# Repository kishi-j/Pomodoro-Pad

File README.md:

# Pomodoro Pad
Pomodoro Pad is a 3 key macropad with a rotary encoder and an OLED Display, using KMK firmware. It will act as a pomodoro timer with a start, pause/resume, and reset button, with the rotary encoder to set the timer length. (The firmware will be updated to work after the parts arrive.)

## CAD Model:

## PCB:

## Schematic:

## BOM:
- 3x Cherry MX Switches
- 3x DSA Keycaps
- 1x 0.91" 128x32 OLED Display
- 1x EC11 Rotary Encoder
- 1x XIAO RP2040
- 1x Case

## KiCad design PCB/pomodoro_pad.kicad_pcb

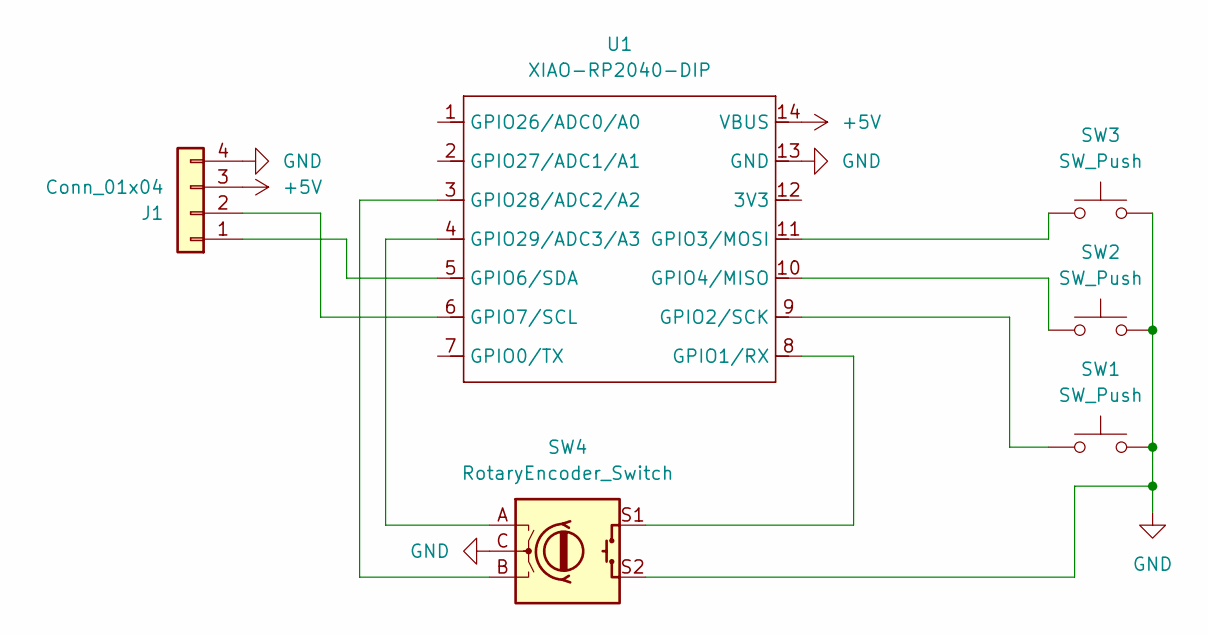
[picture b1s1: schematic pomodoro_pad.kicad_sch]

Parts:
J1: Conn_01x04; SSD1306-0.91-OLED-4pin-128x32
SW1, SW2, SW3: SW_Push; SW_Cherry_MX_1.00u_PCB
SW4: RotaryEncoder_Switch; RotaryEncoder_Alps_EC11E-Switch_Vertical_H20mm
U1: XIAO-RP2040-DIP

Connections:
+5V: J1.3, U1.14 (VBUS)
GND: J1.4, SW1.2, SW2.2, SW3.2, SW4.C, SW4.S2, U1.13 (GND)
unnamed: J1.1, U1.5 (GPIO6/SDA)
unnamed: J1.2, U1.6 (GPIO7/SCL)
unnamed: SW4.S1, U1.8 (GPIO1/RX)
unnamed: SW1.1, U1.9 (GPIO2/SCK)
unnamed: SW3.1, U1.11 (GPIO3/MOSI)
unnamed: SW2.1, U1.10 (GPIO4/MISO)
unnamed: SW4.B, U1.3 (GPIO28/ADC2/A2)
unnamed: SW4.A, U1.4 (GPIO29/ADC3/A3)

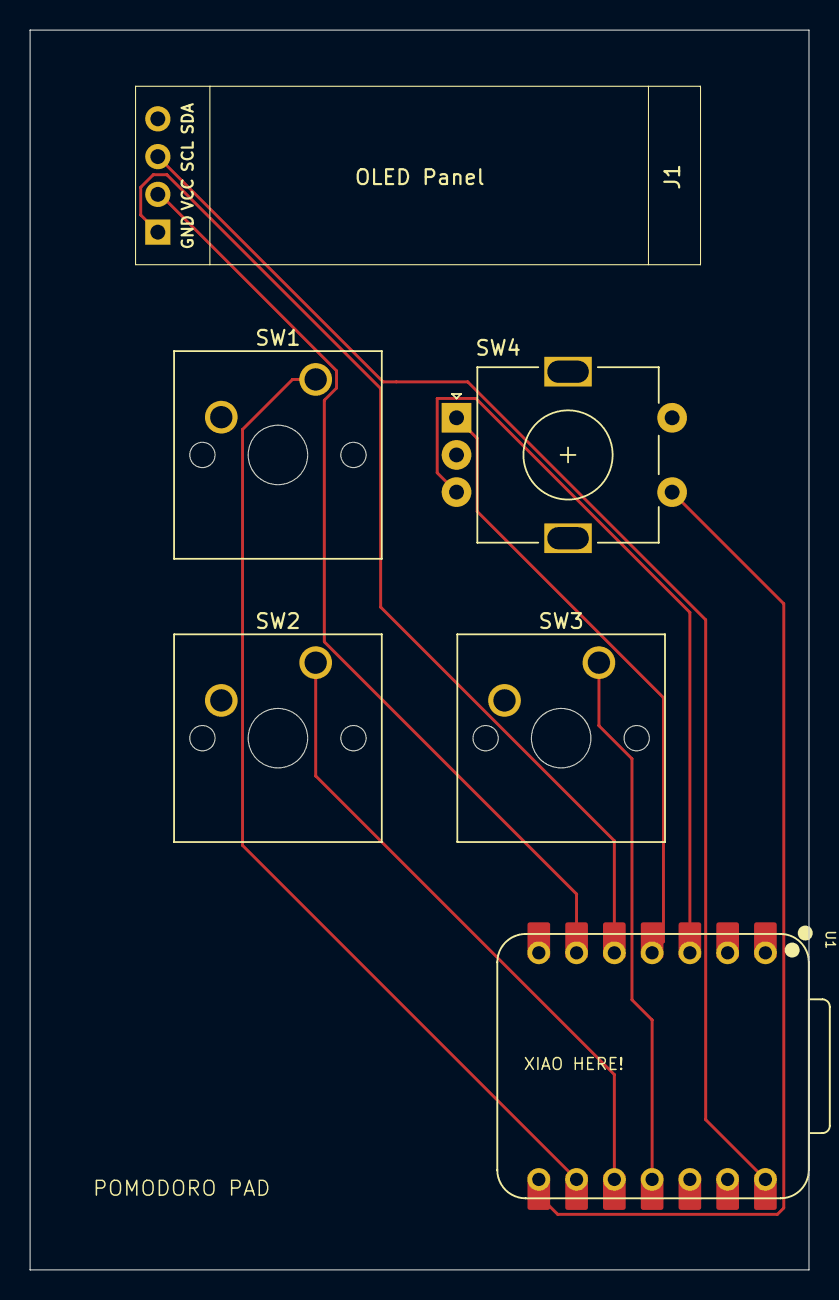
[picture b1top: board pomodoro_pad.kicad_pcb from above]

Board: 2 copper layers, 52.4 x 83.4 mm, 6 parts (0 on the bottom side), 10 nets.

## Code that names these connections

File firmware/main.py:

import board
import displayio
import busio
import adafruit_displayio_ssd1306
from kmk.kmk_keyboard import KMKKeyboard
from kmk.scanners.keypad import KeysScanner
from kmk.modules.encoder import EncoderHandler

displayio.release_displays()

i2c = busio.I2C(scl=board.D7, sda=board.D6)  # GPIO7 = SCL, GPIO6 = SDA
display_bus = displayio.I2CDisplay(i2c, device_address=0x3C)  # 0x3C is default SSD1306 I2C addr
display = adafruit_displayio_ssd1306.SSD1306(display_bus, width=128, height=64)

keyboard = KMKKeyboard()

# SW1, SW2, SW3 → GPIO0, GPIO1, GPIO2
keyboard.matrix = KeysScanner(
    pins=[board.D0, board.D1, board.D2],
    value_when_pressed=False,
)

# A/B/SW → GPIO28, GPIO27, GPIO26
encoder_handler = EncoderHandler()
encoder_handler.pins = (board.D28, board.D27, board.D26, False)
keyboard.modules.append(encoder_handler)

# Run KMK
if __name__ == '__main__':
    keyboard.go()

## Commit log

2025-06-09 Add all folders and files
2025-06-09 updating firmware
